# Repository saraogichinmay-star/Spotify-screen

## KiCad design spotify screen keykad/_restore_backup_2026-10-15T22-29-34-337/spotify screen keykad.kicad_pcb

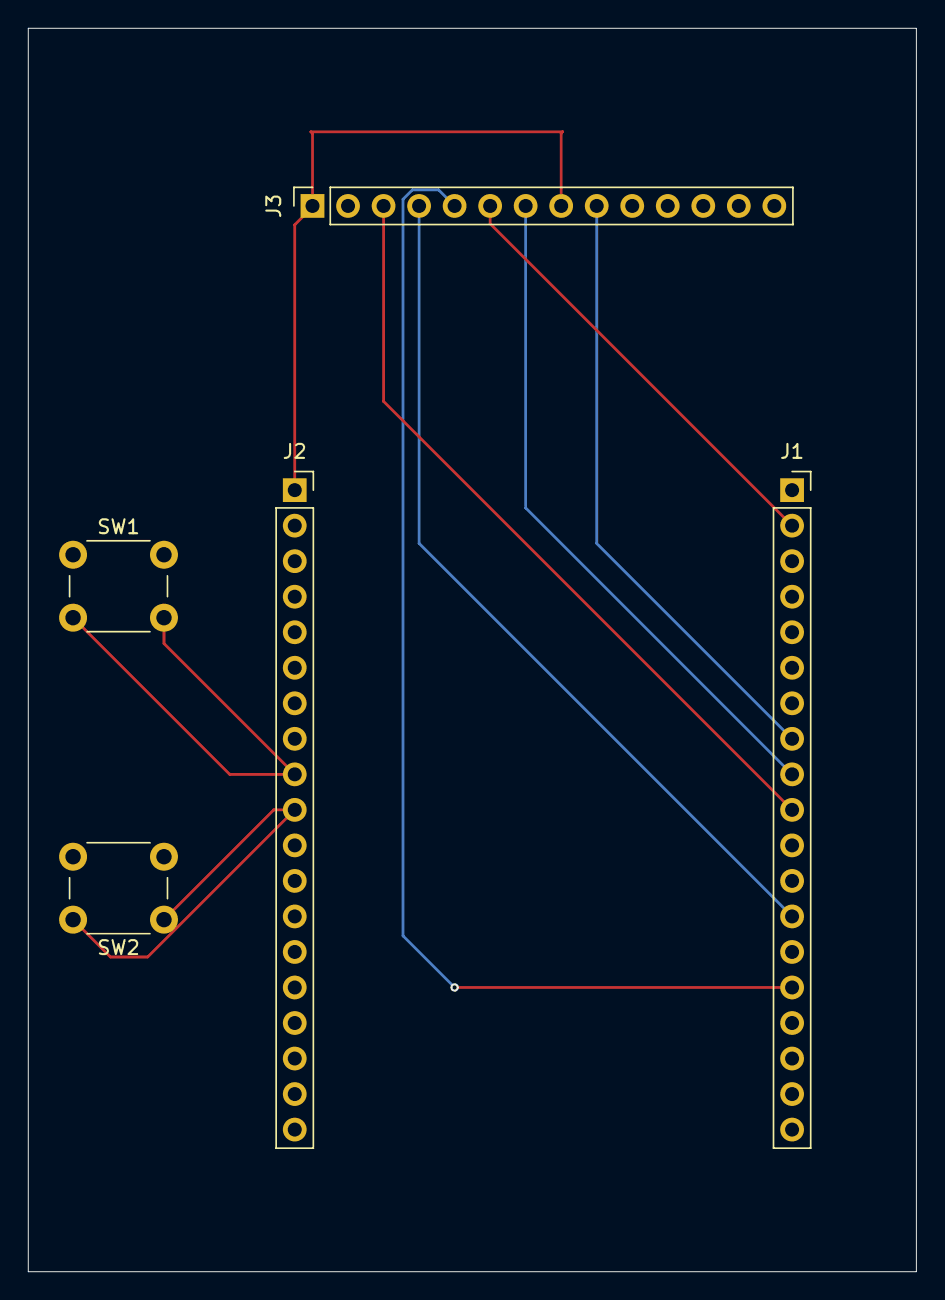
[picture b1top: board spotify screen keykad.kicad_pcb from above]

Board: 2 copper layers, 63.5 x 88.9 mm, 5 parts (0 on the bottom side), 9 nets.

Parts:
J1, J2: Conn_01x19_Socket; PinSocket_1x19_P2.54mm_Vertical
J3: Conn_01x14_Socket; PinSocket_1x14_P2.54mm_Vertical
SW1, SW2: SW_Push; SW_PUSH_6mm

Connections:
/GND: J1.1, J1.7, J3.2, SW1.1, SW2.2
/cs to 5: J1.10, J3.3
/dc to 2: J1.15, J3.5
/led to 3v3: J2.1, J3.1, J3.8
/mi to 19: J1.8, J3.9
/mo to 23: J1.2, J3.6
/play pause to 26: J2.10, SW2.1
/sck to 18: J1.9, J3.7
/song forward to 25: J2.9, SW1.2
